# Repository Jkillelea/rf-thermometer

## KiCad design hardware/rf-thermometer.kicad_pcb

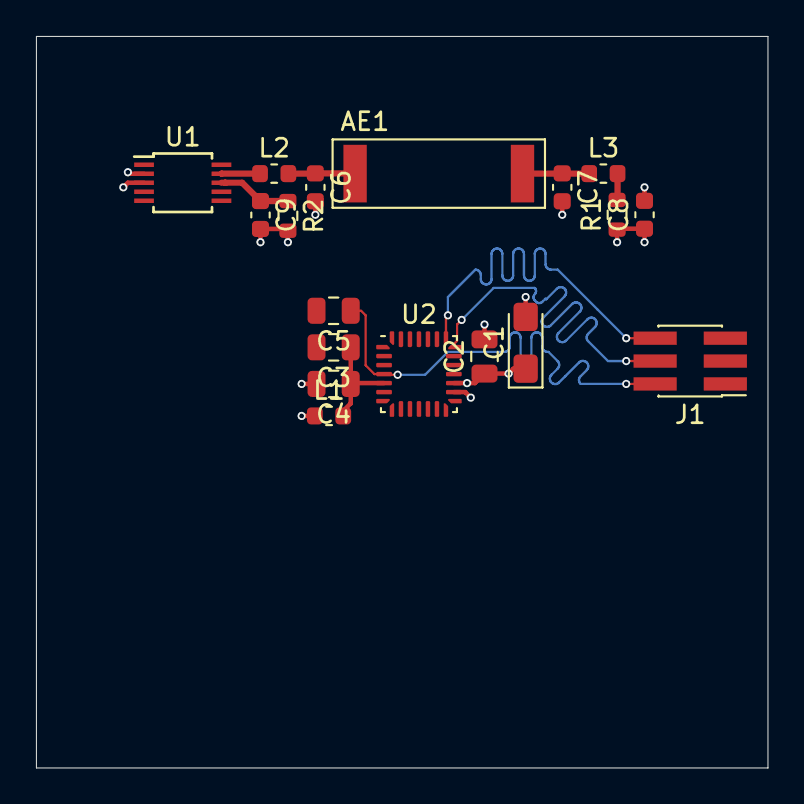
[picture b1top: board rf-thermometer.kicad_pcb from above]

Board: 4 copper layers, 40.6 x 40.6 mm, 18 parts (0 on the bottom side), 11 nets.

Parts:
AE1: Antenna_Loop; Coilcraft_MA5532-AE_RFID
C1: CP; CP_EIA-3216-18_Kemet-A_Pad1.58x1.35mm_HandSolder
C2, C3, C4: C; C_0805_2012Metric
C5: C_Small; C_0805_2012Metric
C6, C7, C8, C9: C_Small; C_0603_1608Metric
J1: Conn_02x03_Odd_Even; PinHeader_2x03_P1.27mm_Vertical_SMD
L1, L2, L3: L_Small; L_0603_1608Metric
R1, R2: R_Small; R_0603_1608Metric
U1: TDA7100; TSSOP-10_3x3mm_P0.5mm
U2: STM32L011G4Ux; QFN-28_4x4mm_P0.5mm

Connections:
+3.3VA: C3.1, C4.1, L1.2, U2.5
+3V3: C1.1, C2.1, C8.1, J1.1, L1.1, R1.1, U1.2, U2.17
/rf_433mhz_50ohm_gnd: C9.1, R2.1, U1.8
/rf_433mhz_50ohm_out: L2.1, U1.9
/rf_ant_hi: AE1.2, C7.1, L3.1
/rf_ant_lo: AE1.1, C6.1, L2.2
GND: C1.2, C2.2, C3.2, C4.2, C5.2, C6.2, C7.2, C8.2, C9.2, J1.5, R2.2, U1.3, U2.16
unnamed: L3.2, R1.2
SWCLK: J1.6, U2.22
SWDIO: J1.4, U2.21
~RST: C5.1, J1.2, U2.4

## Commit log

2020-11-28 Base KiCAD project
2020-11-28 base commits for firmware and software
2020-12-06 Initial firmware commit, from STM32CubeMX code generator
2020-12-06 Apropriate processor with maching pinout to firmware added to schematic
2020-12-06 gitignore
2020-12-06 Add SWDIO/SWCLK pins (for programming and debugging), change line endings
2020-12-06 Add processor datasheet
2020-12-06 Add power bypassing capacitors + filtering inductor for ADC
2020-12-06 NOTATIONAL design based on TDA7100 and Oshpark 4 layer process
2020-12-07 gitignore update
2020-12-07 STM32L0x1 reference manual
2020-12-07 NOTATIONAL add programming header for STM32
